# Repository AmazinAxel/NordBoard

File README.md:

# CH32X035 custom split keyboard

Column staggered Corne-based wired split keyboard

Main features are its single onboard CH32X035G8U6 MCU, USB-C interconnect, lowest-latency-possible yet highly portable ideology, its low cost all while being very ergonomic and comfortable!

A few things this board considers:

- Kalih Choc v1 linear switches
  - Why: for reduced key travel distance and less noise
  - Especially when using in public spaces, clicky switches are kind of obnoxious
- No battery or Bluetooth support, and a SS USB-C interconnect
  - Why: there are a lot of reasons:
  - Batteries are heavy and this would mean expanding the footprint of this design. Right now it's as minimal as it gets, adding wireless support is where things start to get bulky
  - You don't need to worry about charging or latency over bluetooth! Having cables on a desk is almost never a problem if your laptop has a spare port. This is well worth the peace of mind of having to check the keyboard battery, remembering to charge it and having to deal with connecting/disconnecting it.
  - It's the lowest latency you can possibly get. Especially for productivity, every keystroke counts and the faster something updates, the faster you can work.
  - While an audio jack DOES have just enough pins to carry data, ground and power (and is almost always the right choice for this) using a standard port with cables available everywhere allows you to use the interconnect cable for emergencies or other temporary purposes. It is highly versatile. When left in a bag, a 3.5mm headphone cable is basically useless.
  - The SS cable is necessary since it has all the necessary wires to transmit the entire right-half of the keyboard's data without needing to process it on its own half. This means we reduce cost, latency and processing cost and get to carry around a high speed cable with us fo emergencies wherever you travel.
- NOT curved, it's flat and without any key spacing (besides thumb clusters)
  - Why: This is a daily carry item. Therefore a keyboard in your backpack should be light and fit in a small front pocket.
  - Key spacing is good for keeping this compact and minimal key distance means you can fit more keys and access them faster in a smaller form factor
  - It's cheaper to produce the board
- Chocolate [Corne](https://github.com/foostan/crkbd) layout (it's very popular and its design is proven!)
- No row stagger and good column stagger
  - Why: for ergonomics, it curves better to the natural shape of your fingers and hand
  - This is inspired by Corne. Thumb clusters are modified to maximize space, though it might take some getting used to
- No LEDs or rotary encoders or OLED displays (!!)
  - Why: a big goal of this project is to be suuuper cheap. These are gimmicks and add unnecessary cost for no useful benefit. This PCB is designed to be as affordable to produce as possible
- Plateless/no hot-swap sockets
  - Why: This makes the board lighter, thinner and cheaper for carrying, and helps with assembly and keeping it low-profile
  - For me, I never need to swap my switches. I consider this a gimmick in a lot of ways since you can always desolder the switch if it breaks. There's really no reason to have it imo
- CH32X035 (CH32X035G8U6)
  - When this project was named NordBoard, it used a XIAO RP2040 which was kind of overkill since it was a devboard. When optimizing for cost (and complexity) it makes a lot more sense to just have the mcu on the board.
  - I chose a CH32X035G8U6 because its new, well-stocked, _extremely_ cheap (50 cents??) and has enough pins for scanning both sides. It is plenty fast and has USB flashing (and supports HID) and didn't require me to add additional parts for ESD protection since it's all built in.
  - It has flash and a crystal already so there's less components to place and its overall cheaper than something like an RP2040.
  - HOWEVER, the CH32X035 has terrible firmware support and no keyboard firmware supports it right now. I found some Arduino resources that can turn this chip into an HID keyboard emulator, all that's needed is to implement some matrix scanning, keyboard features like layers and then you don't need a big firmware like qmk!
  - This is what makes this board stand out. From what I can tell, this is the first keyboard that uses this new chip. It is better than its counterparts in every way. This keyboard is ahead of its curve!

The advantages of all of the above result in a very well thought-out keyboard for travel and ergonomics. I'm quite proud of the design. I hope you enjoy it too!

## Some renders

[Model available on Onshape](https://cad.onshape.com/documents/24ef5e976496ee201db7b05f/w/fbfc374ac70f5cb67c606ba5/e/005f221e2e9fc59a8e2e02ea)

## PCB & schematic

## Firmware setup

**This keyboard CANNOT run QMK or ZMK or any mainline keyboard firmware!!**

We use a very new chip which does not have support for those firmwares yet. The chip is easily programmable with Platformio and there has been work already to make it work as an HID keyboard device, so I am expanding on that to make this function as a layered keyboard.

First, you need to short the two pads on the top right of the board and plug the device into your computer through a data cable. This puts the device into boot mode so you can flash the firmware.

Clone the repo and go into the conifer/ folder. This is the custom firmware that Snowlayer runs on.

If you are running Nix, I highly recommend running `nix develop` to download deps and setup an environment for running the build.

Run `pio run -t upload`. The firmware should flash to the device, but if you are running Linux and have any issues make sure you add these udev rules:

```nix
SUBSYSTEM=="usb|tty", ATTRS{idVendor}=="1a86", ATTRS{idProduct}=="8010", GROUP:="plugdev"
SUBSYSTEM=="usb|tty", ATTRS{idVendor}=="4348", ATTRS{idProduct}=="55e0", GROUP:="plugdev"
SUBSYSTEM=="usb|tty", ATTRS{idVendor}=="1a86", ATTRS{idProduct}=="8012", GROUP:="plugdev"
SUBSYSTEM=="usb", ATTRS{idVendor}=="1a86", MODE="0666"
```

If you are not able to flash it over USB, I broke out the UART pins on the chip so that you can use a programmer and flash directly to the device. I recommend going over USB though.

Once I finish the firmware I'll attach a screenshot showing the layers and keybinds for common actions. This firmware is only partly complete.

## Bill of Materials

| Part                                 | Where to buy                                           | Cost before tax/shipping | Notes                                                   |
| ------------------------------------ | ------------------------------------------------------ | ------------------------ | ------------------------------------------------------- |
| Keycaps                              | <https://www.aliexpress.us/item/3256809223879113.html> | $20                      | 50pc/1350 V1 A (Does come with 8 extras)                |
| Choc Switches                        | <https://www.aliexpress.us/item/3256808697103313.html> | $25                      | 50pc, blue (Also comes with 8 extras)                   |
| A short C-to-C interconnect          | <https://www.aliexpress.us/item/3256811793020961.html> | $8.93                    | T6A-T6B 20P, 0.25m                                      |
| The board itself!                    | JLCPCB                                                 | $14.70                   | 5 boards, cheapest settings (white PCB)                 |
| CH32X035DS0                          | <https://www.lcsc.com/product-detail/C7437027.html>    | $0.56                    | You only need one for the whole board!                  |
| Switch diodes                        | <https://www.lcsc.com/product-detail/C917030.html>     | $0.50                    | 8 extras                                                |
| 100nF capacitor                      | <https://www.lcsc.com/product-detail/C14663.html>      | $1.27                    | 49 extras, I already have these from a previous project |
| 4.7uF capacitor                      | <https://www.lcsc.com/product-detail/C77077.html>      | $0.68                    | 9 extras                                                |
| 3x 1kO resistors                     | <https://www.lcsc.com/product-detail/C21190.html>      | $0.30                    | 97 extras, I already have these from a previous project |
| 24pin USB-C interconnect receptacles | <https://www.lcsc.com/product-image/C53207800.html>    | $0.4\*2 = $0.81          | No extras                                               |
| 12pin USB-C data receptacle          | <https://www.lcsc.com/product-detail/C5178539.html>    | $0.36                    | 4 extras, I already have some from a previous project   |
|                                      |                                                        | **Total cost: $73.11**   | Does not include tax or shipping, actual cost higher    |

<!-- 20+25+8.93+14.70+0.56+0.5+1.27+0.68+0.3+0.81+0.36 -->

You will need a 3D printer & filament (I recommend blue PLA) for the case. The four mounting holes are 2.2mm radius, 3mm deep, you will need mounting screws for those. The C-C interconnect MUST be Superspeed (like the item above) or else it won't have enough lines so the right half of the board won't work right.

## For fabrication

I have supplied pre built JLCPCB gerbers in `jlcpcb`. Upload the snowlayer.zip there, select a white board, and you're done! Make sure you have all the parts from the BOM.

---

Made for [Forge](https://forge.hackclub.com/projects/827)

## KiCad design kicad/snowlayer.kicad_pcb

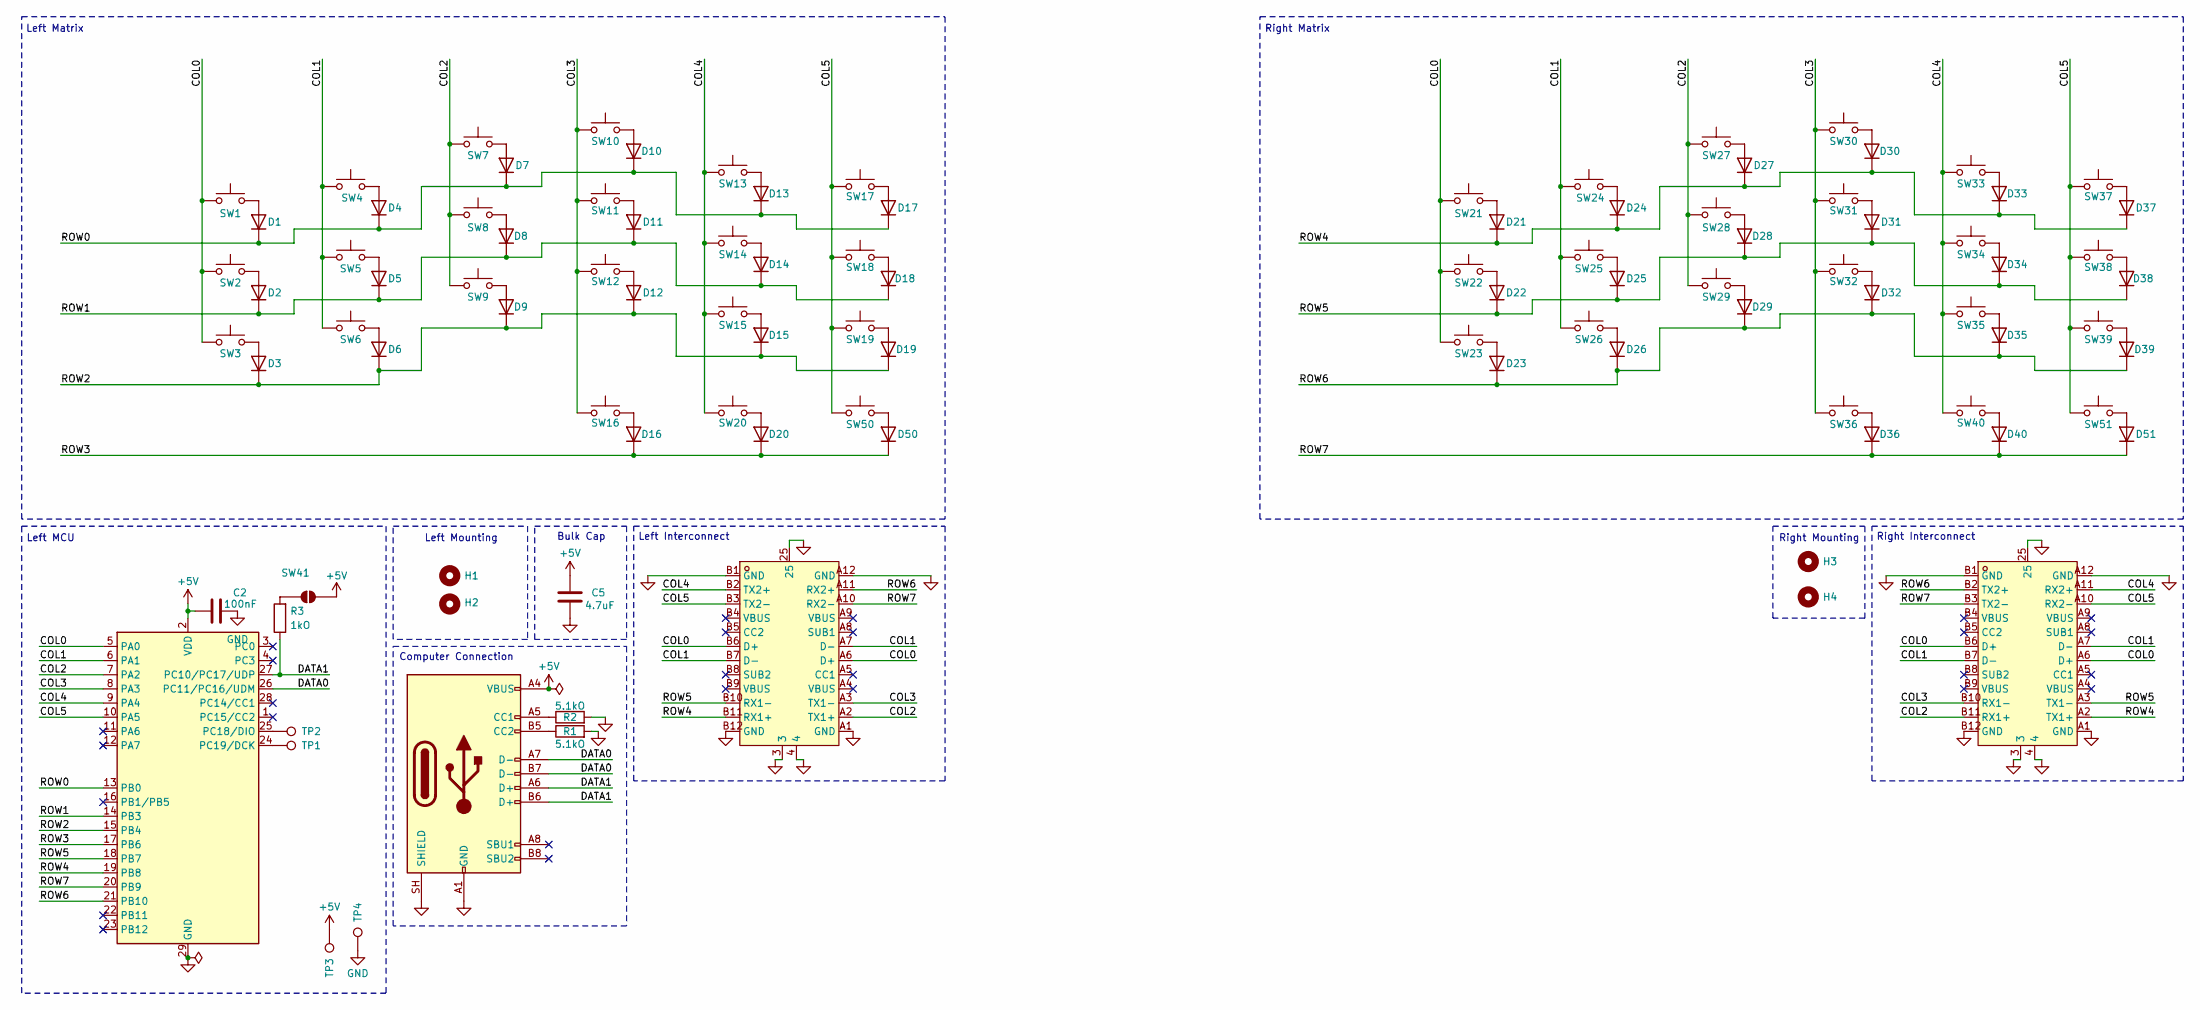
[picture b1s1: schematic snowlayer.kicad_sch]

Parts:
C2: 100nF; C_0603_1608Metric
C5: 4.7uF; C_0805_2012Metric
D1, D2, D3, D4, D5, D6, D7, D8, D9, D10, D11, D12, D13, D14, D15, D16, D17, D18, D19, D20, D21, D22, D23, D24, D25, D26, D27, D28, D29, D30, D31, D32, D33, D34, D35, D36, D37, D38, D39, D40, D50, D51: D; D_SOD-123
H1, H2, H3, H4: MountingHole; MountingHole_2.2mm_M2
P3: USB_C_Plug_USB2.0; USB_C_Receptacle_HRO_TYPE-C-31-M-12
R1, R2: 5.1kO; R_0603_1608Metric
R3: 1kO; R_0603_1608Metric
SW1, SW2, SW3, SW4, SW5, SW6, SW7, SW8, SW9, SW10, SW11, SW12, SW13, SW14, SW15, SW16, SW17, SW18, SW19, SW20, SW21, SW22, SW23, SW24, SW25, SW26, SW27, SW28, SW29, SW30, SW31, SW32, SW33, SW34, SW35, SW36, SW37, SW38, SW39, SW40, SW50, SW51: SW_Push; SW_choc_v1_1u
SW41: SW_Push; SolderJumper-2_P1.3mm_Open_Pad1.0x1.5mm
TP1, TP2, TP3, TP4: TestPoint; TestPoint_Pad_D1.0mm
U1: CH32X035DS0; WQFN-28-1EP_4x4mm_P0.4mm_EP2.7x2.7mm
USB1, USB2: TYPEC-24PIN_C53207800; USB-C-SMD_TYPE-C-24P-QT; MPN TYPEC-24PIN; LCSC Part C53207800

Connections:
+5V: C2.1, C5.1, P3.A4 (VBUS), P3.A9 (VBUS), P3.B4 (VBUS), P3.B9 (VBUS), SW41.2 (B), TP3.1 (1_1), U1.2 (VDD)
/COL0: SW1.1, SW2.1, SW3.1, SW21.1, SW22.1, SW23.1, U1.5 (PA0), USB1.A6 (D+), USB1.B6 (D+), USB2.A6 (D+), USB2.B6 (D+)
/COL1: SW4.1, SW5.1, SW6.1, SW24.1, SW25.1, SW26.1, U1.6 (PA1), USB1.A7 (D-), USB1.B7 (D-), USB2.A7 (D-), USB2.B7 (D-)
/COL2: SW7.1, SW8.1, SW9.1, SW27.1, SW28.1, SW29.1, U1.7 (PA2), USB1.A2 (TX1+), USB2.B11 (RX1+)
/COL3: SW10.1, SW11.1, SW12.1, SW16.1, SW30.1, SW31.1, SW32.1, SW36.1, U1.8 (PA3), USB1.A3 (TX1-), USB2.B10 (RX1-)
/COL4: SW13.1, SW14.1, SW15.1, SW20.1, SW33.1, SW34.1, SW35.1, SW40.1, U1.9 (PA4), USB1.B2 (TX2+), USB2.A11 (RX2+)
/COL5: SW17.1, SW18.1, SW19.1, SW37.1, SW38.1, SW39.1, SW50.1, SW51.1, U1.10 (PA5), USB1.B3 (TX2-), USB2.A10 (RX2-)
/DATA0: P3.A7 (D-), P3.B7 (D-), U1.26 (PC11/PC16/UDM)
/DATA1: P3.A6 (D+), P3.B6 (D+), R3.1, U1.27 (PC10/PC17/UDP)
/ROW0: D1.1 (K), D4.1 (K), D7.1 (K), D10.1 (K), D13.1 (K), D17.1 (K), U1.13 (PB0)
/ROW1: D2.1 (K), D5.1 (K), D8.1 (K), D11.1 (K), D14.1 (K), D18.1 (K), U1.14 (PB3)
/ROW2: D3.1 (K), D6.1 (K), D9.1 (K), D12.1 (K), D15.1 (K), D19.1 (K), U1.15 (PB4)
/ROW3: D16.1 (K), D20.1 (K), D50.1 (K), U1.17 (PB6)
/ROW4: D21.1 (K), D24.1 (K), D27.1 (K), D30.1 (K), D33.1 (K), D37.1 (K), U1.19 (PB8), USB1.B11 (RX1+), USB2.A2 (TX1+)
/ROW5: D22.1 (K), D25.1 (K), D28.1 (K), D31.1 (K), D34.1 (K), D38.1 (K), U1.18 (PB7), USB1.B10 (RX1-), USB2.A3 (TX1-)
/ROW6: D23.1 (K), D26.1 (K), D29.1 (K), D32.1 (K), D35.1 (K), D39.1 (K), U1.21 (PB10), USB1.A11 (RX2+), USB2.B2 (TX2+)
/ROW7: D36.1 (K), D40.1 (K), D51.1 (K), U1.20 (PB9), USB1.A10 (RX2-), USB2.B3 (TX2-)
GND: C2.2, C5.2, P3.A1 (GND), P3.A12 (GND), P3.B1 (GND), P3.B12 (GND), P3.SH (SHIELD), R1.2, R2.2, TP4.1 (1_1), U1.29 (GND), USB1.3, USB1.4, USB1.25, USB1.A1 (GND), USB1.A12 (GND), USB1.B1 (GND), USB1.B12 (GND), USB2.3, USB2.4, USB2.25, USB2.A1 (GND), USB2.A12 (GND), USB2.B1 (GND), USB2.B12 (GND)
unnamed: D1.2 (A), SW1.2
unnamed: D2.2 (A), SW2.2
unnamed: D3.2 (A), SW3.2
unnamed: D4.2 (A), SW4.2
unnamed: D5.2 (A), SW5.2
unnamed: D6.2 (A), SW6.2
unnamed: D7.2 (A), SW7.2
unnamed: D8.2 (A), SW8.2
unnamed: D9.2 (A), SW9.2
unnamed: D10.2 (A), SW10.2
unnamed: D11.2 (A), SW11.2
unnamed: D12.2 (A), SW12.2
unnamed: D13.2 (A), SW13.2
unnamed: D14.2 (A), SW14.2
unnamed: D15.2 (A), SW15.2
unnamed: D16.2 (A), SW16.2
unnamed: D17.2 (A), SW17.2
unnamed: D18.2 (A), SW18.2
unnamed: D19.2 (A), SW19.2
unnamed: D20.2 (A), SW20.2
unnamed: D21.2 (A), SW21.2
unnamed: D22.2 (A), SW22.2
unnamed: D23.2 (A), SW23.2
unnamed: D24.2 (A), SW24.2
unnamed: D25.2 (A), SW25.2
unnamed: D26.2 (A), SW26.2
unnamed: D27.2 (A), SW27.2
unnamed: D28.2 (A), SW28.2
unnamed: D29.2 (A), SW29.2
unnamed: D30.2 (A), SW30.2
unnamed: D31.2 (A), SW31.2
unnamed: D32.2 (A), SW32.2
unnamed: D33.2 (A), SW33.2
unnamed: D34.2 (A), SW34.2
unnamed: D35.2 (A), SW35.2
unnamed: D36.2 (A), SW36.2
unnamed: D37.2 (A), SW37.2
unnamed: D38.2 (A), SW38.2
unnamed: D39.2 (A), SW39.2
unnamed: D40.2 (A), SW40.2
unnamed: D50.2 (A), SW50.2
unnamed: D51.2 (A), SW51.2
unnamed: P3.A5 (CC1), R1.1
unnamed: P3.B5 (CC2), R2.1
unnamed: R3.2, SW41.1 (A)
unnamed: TP2.1 (1_1), U1.25 (PC18/DIO)
unnamed: TP1.1 (1_1), U1.24 (PC19/DCK)

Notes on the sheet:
Left Interconnect
Right Interconnect
Bulk Cap
Left Mounting
Left Matrix
Left MCU
Computer Connection
Right Matrix
Right Mounting

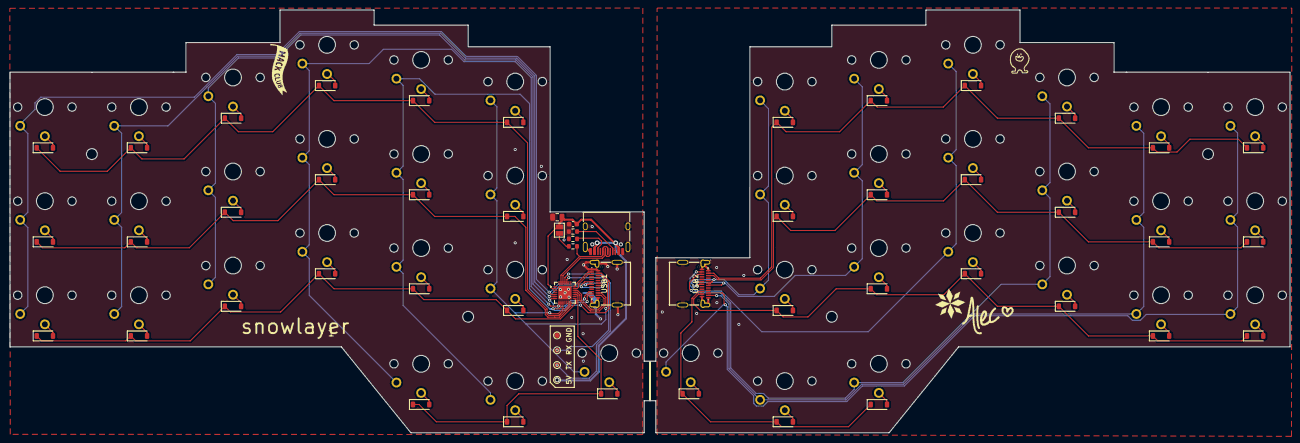
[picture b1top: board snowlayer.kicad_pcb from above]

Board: 2 copper layers, 259.2 x 85.6 mm, 102 parts (0 on the bottom side), 65 nets.

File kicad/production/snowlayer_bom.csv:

Designator,Footprint,Quantity,Value,LCSC Part #
C2,0603,1,100nF,
C5,0805,1,4.7uF,
"D1, D10, D11, D12, D13, D14, D15, D16, D17, D18, D19, D2, D20, D3, D4, D5, D50, D6, D7, D8, D9",D_SOD-123,21,D,
P3,USB_C_Receptacle_HRO_TYPE-C-31-M-12,1,USB_C_Plug_USB2.0,
"R1, R2",0603,2,5.1kO,
R3,0603,1,1kO,
"SW1, SW10, SW11, SW12, SW13, SW14, SW15, SW16, SW17, SW18, SW19, SW2, SW20, SW3, SW4, SW5, SW50, SW6, SW7, SW8, SW9",SW_choc_v1_1u,21,SW_Push,
"TP1, TP2, TP3, TP4",TestPoint_Pad_D1.0mm,4,TestPoint,
U1,WQFN-28-1EP_4x4mm_P0.4mm_EP2.7x2.7mm,1,CH32X035DS0,
USB1,USB-C-SMD_TYPE-C-24P-QT,1,TYPEC-24PIN_C53207800,C53207800

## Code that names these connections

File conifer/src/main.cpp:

#include <Arduino.h>
#include <USBHIDKeyboard.h>

// todo
static const uint8_t ROW_PINS[] = { PA0, PA1 };
static const uint8_t COL_PINS[] = { PA2, PA3 };

#define NUM_ROWS (sizeof(ROW_PINS) / sizeof(ROW_PINS[0]))
#define NUM_COLS (sizeof(COL_PINS) / sizeof(COL_PINS[0]))

static const uint8_t KEYMAP[NUM_ROWS][NUM_COLS] = {
  { 'a', 'b' },
  { 'c', KEY_RETURN },
};

// Debounce: number of consecutive identical scans before a change is accepted.
static const uint8_t DEBOUNCE_SCANS = 5;

// ---------------------------------------------------------------------------
static bool    keyDown[NUM_ROWS][NUM_COLS];   // current stable state
static uint8_t stableCount[NUM_ROWS][NUM_COLS];
static bool    lastRead[NUM_ROWS][NUM_COLS];

void setup() {
  for (uint8_t r = 0; r < NUM_ROWS; r++) {
    pinMode(ROW_PINS[r], OUTPUT);
    digitalWrite(ROW_PINS[r], HIGH);          // inactive (not selected)
  }
  for (uint8_t c = 0; c < NUM_COLS; c++) {
    pinMode(COL_PINS[c], INPUT_PULLUP);
  }

  for (uint8_t r = 0; r < NUM_ROWS; r++)
    for (uint8_t c = 0; c < NUM_COLS; c++) {
      keyDown[r][c] = lastRead[r][c] = false;
      stableCount[r][c] = 0;
    }

  Keyboard.begin();
  delay(1000);                                // let the host enumerate
}

void loop() {
  for (uint8_t r = 0; r < NUM_ROWS; r++) {
    digitalWrite(ROW_PINS[r], LOW);           // select this row
    delayMicroseconds(5);                     // let the line settle

    for (uint8_t c = 0; c < NUM_COLS; c++) {
      bool pressed = (digitalRead(COL_PINS[c]) == LOW);

      if (pressed == lastRead[r][c]) {
        if (stableCount[r][c] < DEBOUNCE_SCANS) stableCount[r][c]++;
      } else {
        stableCount[r][c] = 0;
        lastRead[r][c] = pressed;
      }

      // Commit a change only once it has been stable long enough.
      if (stableCount[r][c] >= DEBOUNCE_SCANS && keyDown[r][c] != pressed) {
        keyDown[r][c] = pressed;
        uint8_t k = KEYMAP[r][c];
        if (k) {
          if (pressed) Keyboard.press(k);
          else         Keyboard.release(k);
        }
      }
    }

    digitalWrite(ROW_PINS[r], HIGH);          // deselect
  }
}

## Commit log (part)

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2026-02-14 init
2026-02-14 feat: readme & begin project
2026-02-15 sync
2026-02-15 feat: PCB
2026-02-15 feat: work on schem layout
2026-02-15 feat: schem
2026-02-15 feat: finish schem, finish PCB layout
2026-02-16 chore: cleanup
2026-02-16 feat: finish pcb layout and cleanup todo routing
2026-02-16 feat: finish board routing
2026-02-16 feat: new col in schem (not in PCB)
2026-02-16 feat: revamp schem
2026-02-18 feat(v1): finish PCB layout
2026-02-18 chore: pcb board cleanup
2026-02-18 feat: implement mousebites
2026-02-18 feat: finish PCB awaiting peer review + silkscreen
2026-02-19 feat: finish PCB silkscreen, export STEP
2026-02-19 fix: fix pcb errors
2026-06-16 feat: add JOURNAL.md
2026-06-16 chore: upd journal
2026-06-17 journal and some work
2026-06-24 major feat: completely restructure project, new switches, no more path hardcoding
2026-06-25 feat: new journal, fix some errors, usb-c interconnect, new edge cuts and so much more
2026-06-25 feat: interconnect cable, new journal
2026-06-26 feat: new journal, finish PCB
2026-06-26 feat: readme
2026-06-26 feat: switch to 5.1k resistor, fix all 3D models
2026-06-26 chore: impove traces, cleanup
2026-06-26 fix: update pcb traces
2026-06-27 feat: gerbers, new journal, update readme, finish BOM
2026-06-27 feat: firmware, final journal entry, remove gerbers, cleanup schematic
2026-06-27 fix: update journal
2026-06-28 chore: update readme, add C-to-C interconnect to BOM
